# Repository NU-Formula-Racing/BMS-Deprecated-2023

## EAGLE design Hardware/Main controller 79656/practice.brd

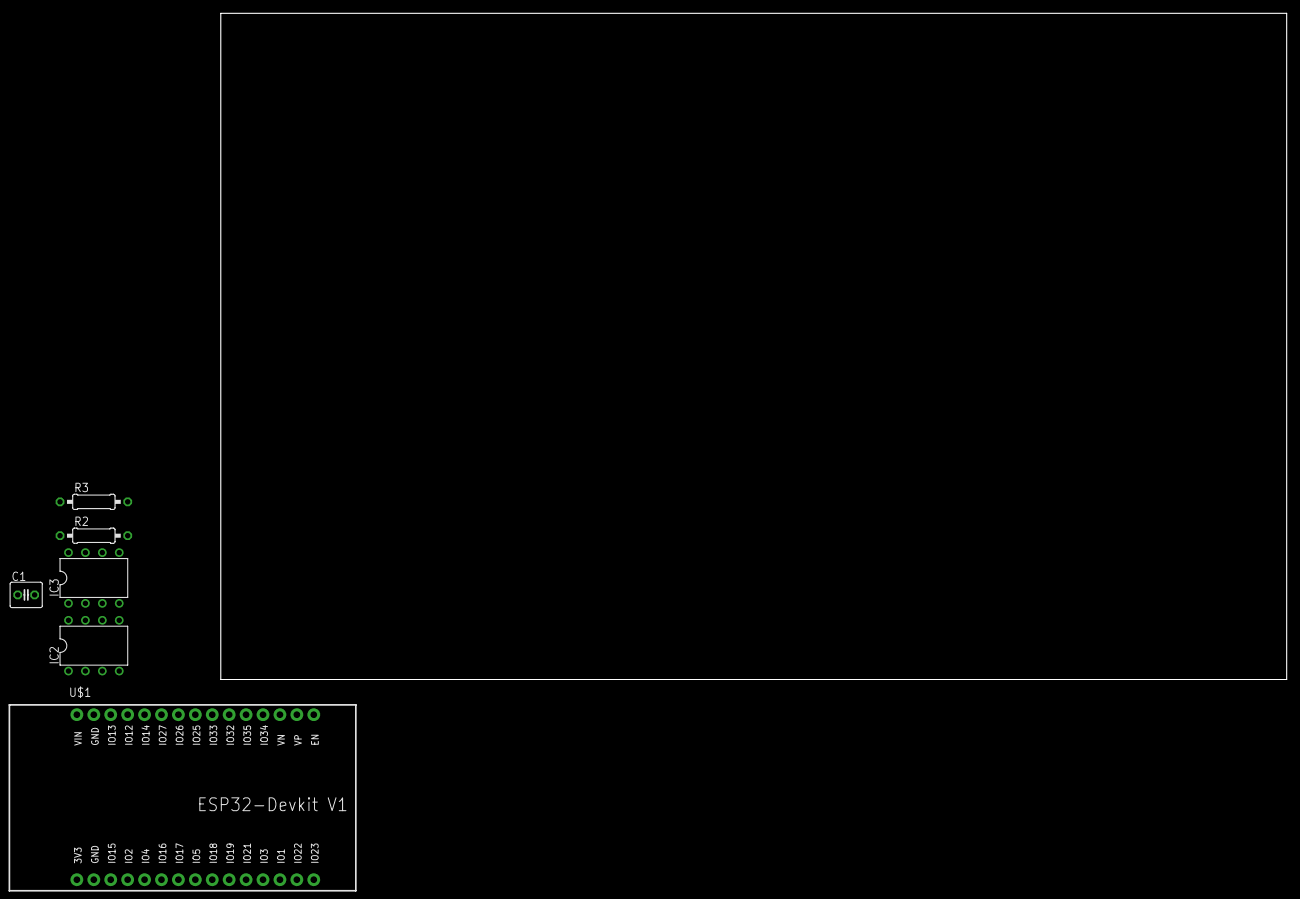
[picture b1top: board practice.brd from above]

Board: 2 copper layers, 160.0 x 100.0 mm, 6 parts (0 on the bottom side), 7 nets, no tracks yet.

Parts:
C1: C025-040X050
IC2, IC3: LM741P; DIL08
R2, R3: 0207/10
U$1: ESP32DEVKITV1; ESP32-DEVKITV1

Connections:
unnamed: IC2.5, IC3.5
unnamed: IC2.1, IC3.1
unnamed: IC2.2, IC2.6, IC3.2, IC3.6
unnamed: IC2.8, IC3.8
unnamed: IC2.7, IC3.7
unnamed: IC2.4, IC3.4
unnamed: C1.1, IC2.3, IC3.3, R2.1, R3.2

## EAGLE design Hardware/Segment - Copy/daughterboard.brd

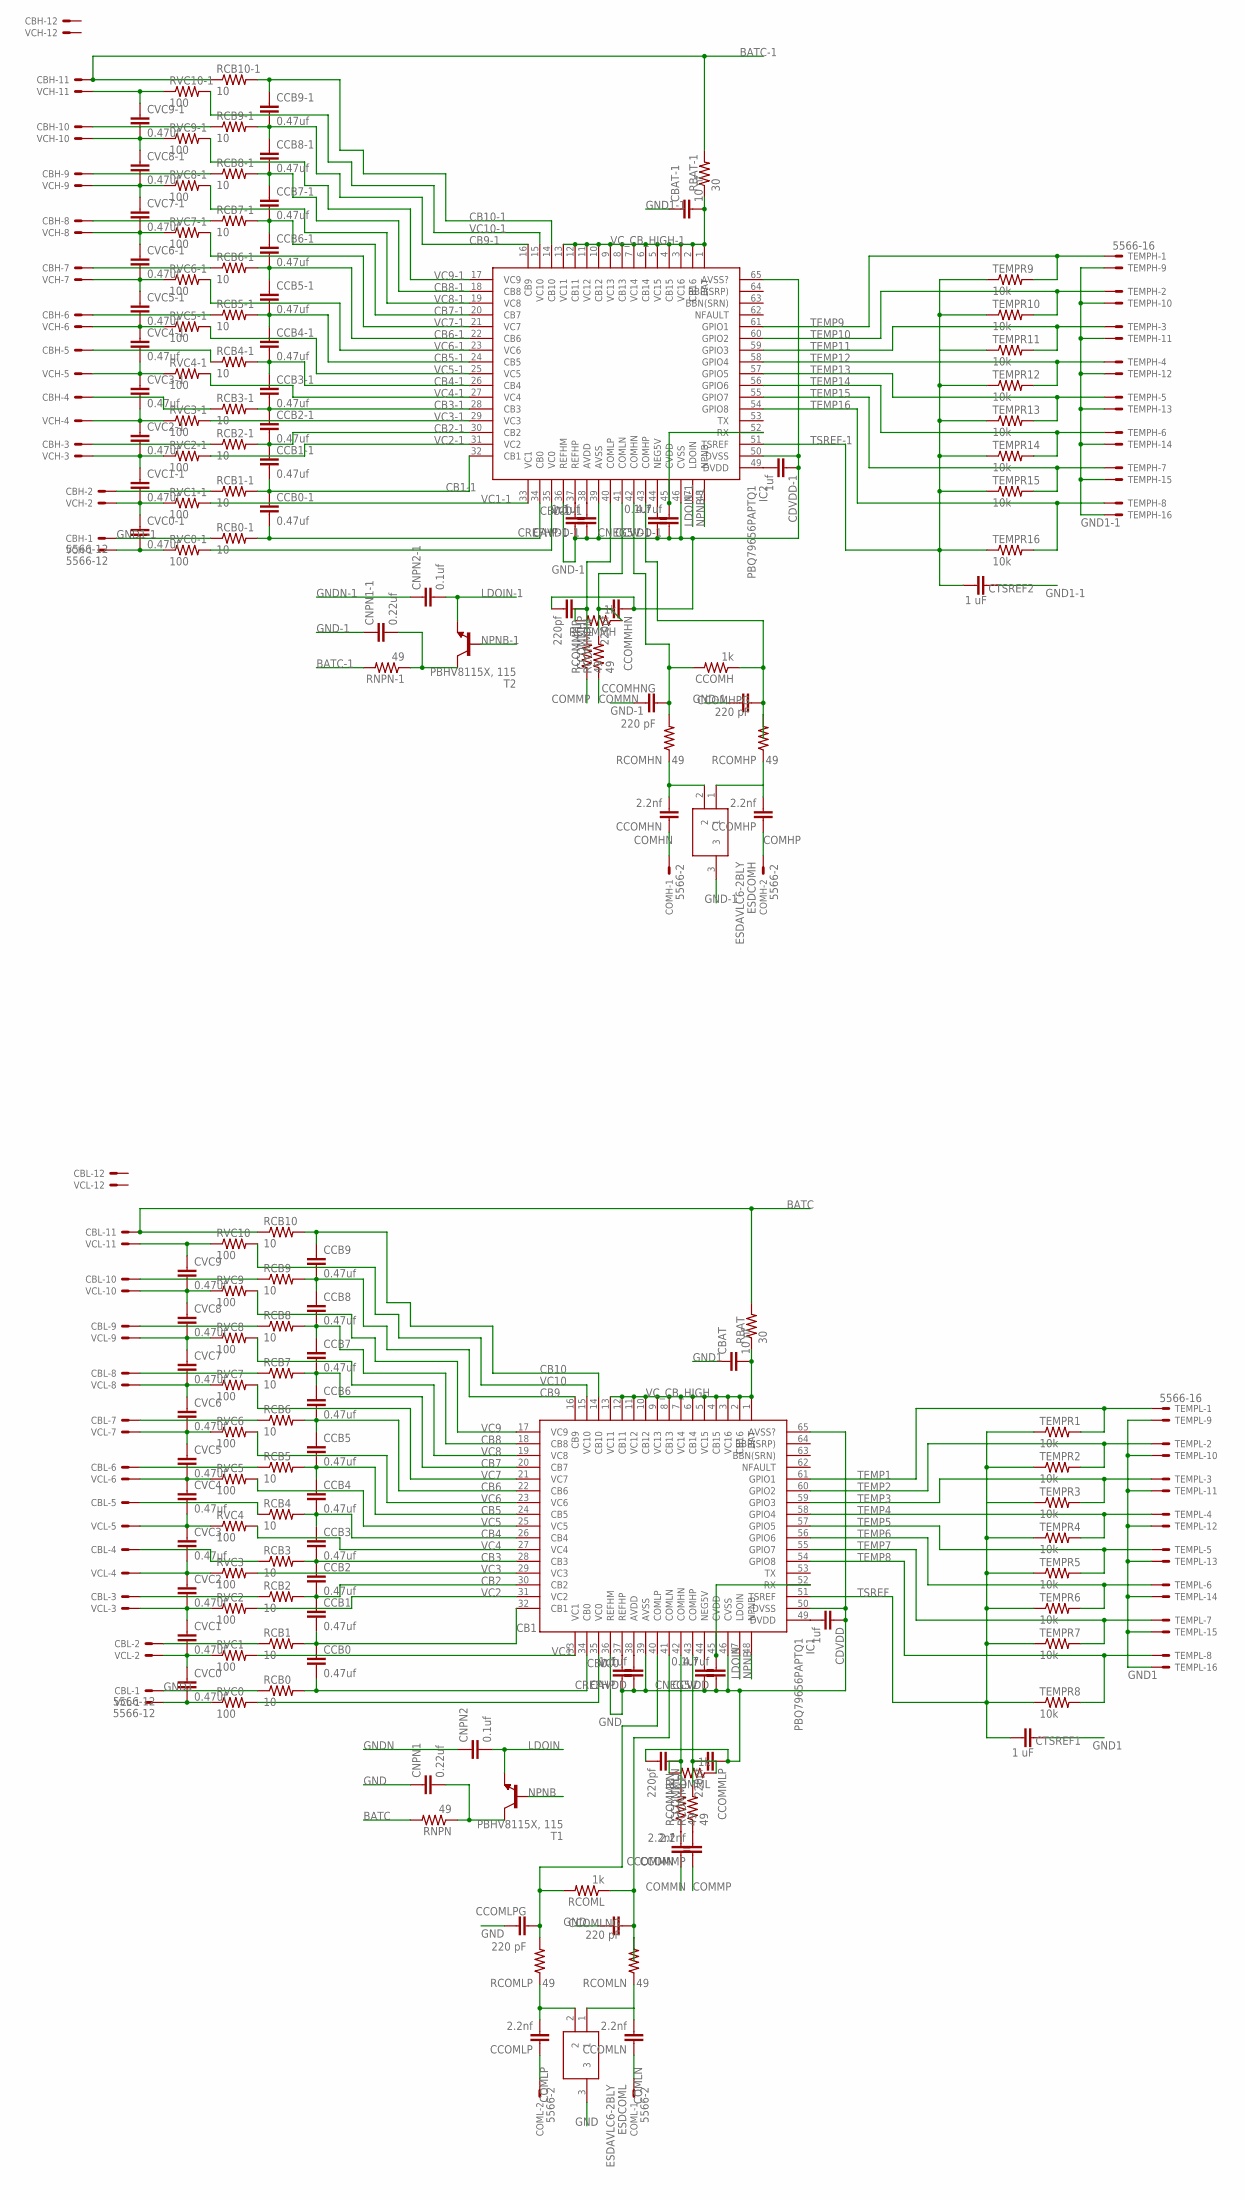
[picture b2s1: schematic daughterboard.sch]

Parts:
CAVDD: 1uf; C0603
CAVDD-1: 1uf; C0603
CBAT: 10 nf; C0603
CBAT-1: 10 nf; C0603
CBH: 5566-12
CBL: 5566-12
CCB0, CCB0-1, CCB1, CCB1-1, CCB2, CCB2-1, CCB3, CCB3-1, CCB4, CCB4-1, CCB5, CCB5-1, CCB6, CCB6-1, CCB7, CCB7-1, CCB8, CCB8-1, CCB9, CCB9-1: 0.47uf; C0603
CCOMH: 1k; R0603
CCOMHN: 2.2nf; C0603
CCOMHNG: 220 pF; C0603
CCOMHP: 2.2nf; C0603
CCOMHPG: 220 pF; C0603
CCOMLN: 2.2nf; C0603
CCOMLNG: 220 pF; C0603
CCOMLP: 2.2nf; C0603
CCOMLPG: 220 pF; C0603
CCOMMHN: 220pf; C0603
CCOMMHP: 220pf; C0603
CCOMMLN: 220pf; C0603
CCOMMLP: 220pf; C0603
CCOMMN: 2.2nf; C0603
CCOMMP: 2.2nf; C0603
CCVDD: 4.7uf; C0603
CCVDD-1: 4.7uf; C0603
CDVDD: 1uf; C0603
CDVDD-1: 1uf; C0603
CNEG5V, CNEG5V-1: 0.1uf; C0603
CNPN1, CNPN1-1: 0.22uf; C0603
CNPN2, CNPN2-1: 0.1uf; C0603
COMH: 5566-2
COML: 5566-2
CREFHP: 1uf; C0603
CREFHP-1: 1uf; C0603
CTSREF1, CTSREF2: 1 uF; C0603
CVC0, CVC0-1, CVC1, CVC1-1, CVC2, CVC2-1, CVC3, CVC3-1, CVC4, CVC4-1, CVC5, CVC5-1, CVC6, CVC6-1, CVC7, CVC7-1, CVC8, CVC8-1, CVC9, CVC9-1: 0.47uf; C0603
ESDCOMH: ESDAVLC6-2BLY; SOT95P255X150-3N
ESDCOML: ESDAVLC6-2BLY; SOT95P255X150-3N
IC1, IC2: PBQ79656PAPTQ1; QFP50P1200X1200X120-65N
RBAT: 30; R0603
RBAT-1: 30; R0603
RCB0, RCB0-1, RCB1, RCB1-1, RCB2, RCB2-1, RCB3, RCB3-1, RCB4, RCB4-1, RCB5, RCB5-1, RCB6, RCB6-1, RCB7, RCB7-1, RCB8, RCB8-1, RCB9, RCB9-1, RCB10, RCB10-1: 10; R1210
RCOMHN: 49; R0603
RCOMHP: 49; R0603
RCOML: 1k; R0603
RCOMLN: 49; R0603
RCOMLP: 49; R0603
RCOMMH: 1k; R0603
RCOMMHN: 49; R0603
RCOMMHP: 49; R0603
RCOMML: 1k; R0603
RCOMMLN: 49; R0603
RCOMMLP: 49; R0603
RNPN: 49; R0603
RNPN-1: 49; R0603
RVC0, RVC0-1, RVC1, RVC1-1, RVC2, RVC2-1, RVC3, RVC3-1, RVC4, RVC4-1, RVC5, RVC5-1, RVC6, RVC6-1, RVC7, RVC7-1, RVC8, RVC8-1, RVC9, RVC9-1, RVC10, RVC10-1: 100; R0603
T1, T2: PBHV8115X, 115; SOT89-BCE
TEMPH: 5566-16
TEMPL: 5566-16
TEMPR1, TEMPR2, TEMPR3, TEMPR4, TEMPR5, TEMPR6, TEMPR7, TEMPR8, TEMPR9, TEMPR10, TEMPR11, TEMPR12, TEMPR13, TEMPR14, TEMPR15, TEMPR16: 10k; R0603
VCH: 5566-12
VCL: 5566-12

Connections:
BATC: CBL.11, RBAT.2, RCB10.1, RNPN.2
BATC-1: CBH.11, RBAT-1.2, RCB10-1.1, RNPN-1.2
CB0: CCB0.2, IC1.34 (CB0), RCB0.2
CB0-1: CCB0-1.2, IC2.34 (CB0), RCB0-1.2
CB1: CCB0.1, CCB1.2, IC1.32 (CB1), RCB1.2
CB1-1: CCB0-1.1, CCB1-1.2, IC2.32 (CB1), RCB1-1.2
CB2: CCB1.1, CCB2.2, IC1.30 (CB2), RCB2.2
CB2-1: CCB1-1.1, CCB2-1.2, IC2.30 (CB2), RCB2-1.2
CB3: CCB2.1, CCB3.2, IC1.28 (CB3), RCB3.2
CB3-1: CCB2-1.1, CCB3-1.2, IC2.28 (CB3), RCB3-1.2
CB4: CCB3.1, CCB4.2, IC1.26 (CB4), RCB4.2
CB4-1: CCB3-1.1, CCB4-1.2, IC2.26 (CB4), RCB4-1.2
CB5: CCB4.1, CCB5.2, IC1.24 (CB5), RCB5.2
CB5-1: CCB4-1.1, CCB5-1.2, IC2.24 (CB5), RCB5-1.2
CB6: CCB5.1, CCB6.2, IC1.22 (CB6), RCB6.2
CB6-1: CCB5-1.1, CCB6-1.2, IC2.22 (CB6), RCB6-1.2
CB7: CCB6.1, CCB7.2, IC1.20 (CB7), RCB7.2
CB7-1: CCB6-1.1, CCB7-1.2, IC2.20 (CB7), RCB7-1.2
CB8: CCB7.1, CCB8.2, IC1.18 (CB8), RCB8.2
CB8-1: CCB7-1.1, CCB8-1.2, IC2.18 (CB8), RCB8-1.2
CB9: CCB8.1, CCB9.2, IC1.16 (CB9), RCB9.2
CB9-1: CCB8-1.1, CCB9-1.2, IC2.16 (CB9), RCB9-1.2
CB10: CCB9.1, IC1.14 (CB10), RCB10.2
CB10-1: CCB9-1.1, IC2.14 (CB10), RCB10-1.2
COMHN: CCOMHN.1, COMH.1
COMHP: CCOMHP.1, COMH.2
COMLN: CCOMLN.1, COML.1
COMLP: CCOMLP.1, COML.2
COMMN: CCOMMN.1, RCOMMHN.1
COMMP: CCOMMP.1, RCOMMHP.1
CVDD: CCVDD.2, IC1.45 (CVDD), IC1.52 (RX)
CVDD-1: CCVDD-1.2, IC2.45 (CVDD), IC2.52 (RX)
GND: CAVDD.1, CCOMLNG.1, CCOMLPG.1, CCOMMLN.2, CCOMMLP.1, CCVDD.1, CDVDD.1, CNEG5V.1, CNPN1.1, CREFHP.1, ESDCOML.3, IC1.36 (REFHM), IC1.39 (AVSS), IC1.46 (CVSS), IC1.50 (DVSS), IC1.65 (AVSS?)
GND1: CBAT.1, CBL.1, CTSREF1.1, RCB0.1, TEMPL.9, TEMPL.10, TEMPL.11, TEMPL.12, TEMPL.13, TEMPL.14, TEMPL.15, TEMPL.16
GND1-1: CBAT-1.1, CBH.1, CTSREF2.1, RCB0-1.1, TEMPH.9, TEMPH.10, TEMPH.11, TEMPH.12, TEMPH.13, TEMPH.14, TEMPH.15, TEMPH.16
GND-1: CAVDD-1.1, CCOMHNG.1, CCOMHPG.1, CCOMMHN.1, CCOMMHP.2, CCVDD-1.1, CDVDD-1.1, CNEG5V-1.1, CNPN1-1.1, CREFHP-1.1, ESDCOMH.3, IC2.36 (REFHM), IC2.39 (AVSS), IC2.46 (CVSS), IC2.50 (DVSS), IC2.65 (AVSS?)
GNDN: CNPN2.1
GNDN-1: CNPN2-1.1
LDOIN: CNPN2.2, IC1.47 (LDOIN), T1.E
LDOIN-1: CNPN2-1.2, IC2.47 (LDOIN), T2.E
unnamed: CBL.2, RCB1.1
unnamed: CBL.3, RCB2.1
unnamed: CBL.4, RCB3.1
unnamed: CBL.5, RCB4.1
unnamed: CBL.6, RCB5.1
unnamed: CBL.9, RCB8.1
unnamed: CBL.10, RCB9.1
unnamed: CBL.7, RCB6.1
unnamed: CCOMLNG.2, IC1.41 (COMLN), RCOML.1, RCOMLN.2
unnamed: CBL.8, RCB7.1
unnamed: CREFHP.2, IC1.37 (REFHP)
unnamed: CVC0.2, RVC0.1, VCL.1
unnamed: CVC0.1, CVC1.2, RVC1.1, VCL.2
unnamed: CVC1.1, CVC2.2, RVC2.1, VCL.3
unnamed: CVC2.1, CVC3.2, RVC3.1, VCL.4
unnamed: CVC3.1, CVC4.2, RVC4.1, VCL.5
unnamed: CVC4.1, CVC5.2, RVC5.1, VCL.6
unnamed: CVC5.1, CVC6.2, RVC6.1, VCL.7
unnamed: CVC6.1, CVC7.2, RVC7.1, VCL.8
unnamed: CVC7.1, CVC8.2, RVC8.1, VCL.9
unnamed: CVC8.1, CVC9.2, RVC9.1, VCL.10
unnamed: CVC9.1, RVC10.1, VCL.11
unnamed: CAVDD.2, IC1.38 (AVDD)
unnamed: CNEG5V.2, IC1.44 (NEG5V)
unnamed: CCOMLPG.2, IC1.40 (COMLP), RCOML.2, RCOMLP.2
unnamed: CDVDD.2, IC1.49 (DVDD)
unnamed: CCOMMLN.1, IC1.42 (COMHN), RCOMML.2, RCOMMLN.2
unnamed: CCOMMLP.2, IC1.43 (COMHP), RCOMML.1, RCOMMLP.2
unnamed: CCOMMN.2, RCOMMLN.1
unnamed: CCOMMP.2, RCOMMLP.1
unnamed: CNPN1.2, RNPN.1, T1.C
unnamed: CCOMLP.2, ESDCOML.2, RCOMLP.1
unnamed: CCOMLN.2, ESDCOML.1, RCOMLN.1
unnamed: CBH.3, RCB2-1.1
unnamed: CBH.2, RCB1-1.1
unnamed: CBH.4, RCB3-1.1
unnamed: CBH.5, RCB4-1.1
unnamed: CBH.6, RCB5-1.1
unnamed: CBH.7, RCB6-1.1
unnamed: CBH.8, RCB7-1.1
unnamed: CBH.9, RCB8-1.1
unnamed: CBH.10, RCB9-1.1
unnamed: CVC0-1.2, RVC0-1.1, VCH.1
unnamed: CVC0-1.1, CVC1-1.2, RVC1-1.1, VCH.2
unnamed: CVC1-1.1, CVC2-1.2, RVC2-1.1, VCH.3
unnamed: CVC2-1.1, CVC3-1.2, RVC3-1.1, VCH.4
unnamed: CVC3-1.1, CVC4-1.2, RVC4-1.1, VCH.5
unnamed: CVC4-1.1, CVC5-1.2, RVC5-1.1, VCH.6
unnamed: CVC5-1.1, CVC6-1.2, RVC6-1.1, VCH.7
unnamed: CVC6-1.1, CVC7-1.2, RVC7-1.1, VCH.8
unnamed: CVC7-1.1, CVC8-1.2, RVC8-1.1, VCH.9
unnamed: CVC8-1.1, CVC9-1.2, RVC9-1.1, VCH.10
unnamed: CVC9-1.1, RVC10-1.1, VCH.11
unnamed: CREFHP-1.2, IC2.37 (REFHP)
unnamed: CAVDD-1.2, IC2.38 (AVDD)
unnamed: CNEG5V-1.2, IC2.44 (NEG5V)
unnamed: CDVDD-1.2, IC2.49 (DVDD)
unnamed: CCOMMHN.2, IC2.41 (COMLN), RCOMMH.1, RCOMMHN.2
unnamed: CCOMMHP.1, IC2.40 (COMLP), RCOMMH.2, RCOMMHP.2
unnamed: CNPN1-1.2, RNPN-1.1, T2.C
unnamed: CCOMH.1, CCOMHPG.2, IC2.43 (COMHP), RCOMHP.2
unnamed: CCOMH.2, CCOMHNG.2, IC2.42 (COMHN), RCOMHN.2
unnamed: CCOMHN.2, ESDCOMH.2, RCOMHN.1
unnamed: CCOMHP.2, ESDCOMH.1, RCOMHP.1
NPNB: IC1.48 (NPNB), T1.B
NPNB-1: IC2.48 (NPNB), T2.B
TEMP1: IC1.61 (GPIO1), TEMPL.1, TEMPR1.2
TEMP2: IC1.60 (GPIO2), TEMPL.2, TEMPR2.2
TEMP3: IC1.59 (GPIO3), TEMPL.3, TEMPR3.2
TEMP4: IC1.58 (GPIO4), TEMPL.4, TEMPR4.2
TEMP5: IC1.57 (GPIO5), TEMPL.5, TEMPR5.2
TEMP6: IC1.56 (GPIO6), TEMPL.6, TEMPR6.2
TEMP7: IC1.55 (GPIO7), TEMPL.7, TEMPR7.2
TEMP8: IC1.54 (GPIO8), TEMPL.8, TEMPR8.2
TEMP9: IC2.61 (GPIO1), TEMPH.1, TEMPR9.2
TEMP10: IC2.60 (GPIO2), TEMPH.2, TEMPR10.2
TEMP11: IC2.59 (GPIO3), TEMPH.3, TEMPR11.2
TEMP12: IC2.58 (GPIO4), TEMPH.4, TEMPR12.2
TEMP13: IC2.57 (GPIO5), TEMPH.5, TEMPR13.2
TEMP14: IC2.56 (GPIO6), TEMPH.6, TEMPR14.2
TEMP15: IC2.55 (GPIO7), TEMPH.7, TEMPR15.2
TEMP16: IC2.54 (GPIO8), TEMPH.8, TEMPR16.2
TSREF: CTSREF1.2, IC1.51 (TSREF), TEMPR1.1, TEMPR2.1, TEMPR3.1, TEMPR4.1, TEMPR5.1, TEMPR6.1, TEMPR7.1, TEMPR8.1
TSREF-1: CTSREF2.2, IC2.51 (TSREF), TEMPR9.1, TEMPR10.1, TEMPR11.1, TEMPR12.1, TEMPR13.1, TEMPR14.1, TEMPR15.1, TEMPR16.1
VC0: IC1.35 (VC0), RVC0.2
VC0-1: IC2.35 (VC0), RVC0-1.2
VC1: IC1.33 (VC1), RVC1.2
VC1-1: IC2.33 (VC1), RVC1-1.2
VC2: IC1.31 (VC2), RVC2.2
VC2-1: IC2.31 (VC2), RVC2-1.2
VC3: IC1.29 (VC3), RVC3.2
VC3-1: IC2.29 (VC3), RVC3-1.2
VC4: IC1.27 (VC4), RVC4.2
VC4-1: IC2.27 (VC4), RVC4-1.2
VC5: IC1.25 (VC5), RVC5.2
VC5-1: IC2.25 (VC5), RVC5-1.2
VC6: IC1.23 (VC6), RVC6.2
VC6-1: IC2.23 (VC6), RVC6-1.2
VC7: IC1.21 (VC7), RVC7.2
VC7-1: IC2.21 (VC7), RVC7-1.2
VC8: IC1.19 (VC8), RVC8.2
VC8-1: IC2.19 (VC8), RVC8-1.2
VC9: IC1.17 (VC9), RVC9.2
VC9-1: IC2.17 (VC9), RVC9-1.2
VC10: IC1.15 (VC10), RVC10.2
VC10-1: IC2.15 (VC10), RVC10-1.2
VC_CB_HIGH: CBAT.2, IC1.1 (BAT), IC1.2 (CB16), IC1.3 (VC16), IC1.4 (CB15), IC1.5 (VC15), IC1.6 (CB14), IC1.7 (VC14), IC1.8 (CB13), IC1.9 (VC13), IC1.10 (CB12), IC1.11 (VC12), IC1.12 (CB11), IC1.13 (VC11), RBAT.1
VC_CB_HIGH-1: CBAT-1.2, IC2.1 (BAT), IC2.2 (CB16), IC2.3 (VC16), IC2.4 (CB15), IC2.5 (VC15), IC2.6 (CB14), IC2.7 (VC14), IC2.8 (CB13), IC2.9 (VC13), IC2.10 (CB12), IC2.11 (VC12), IC2.12 (CB11), IC2.13 (VC11), RBAT-1.1

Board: 2 copper layers, 162 parts (0 on the bottom side), 146 nets, no tracks yet.

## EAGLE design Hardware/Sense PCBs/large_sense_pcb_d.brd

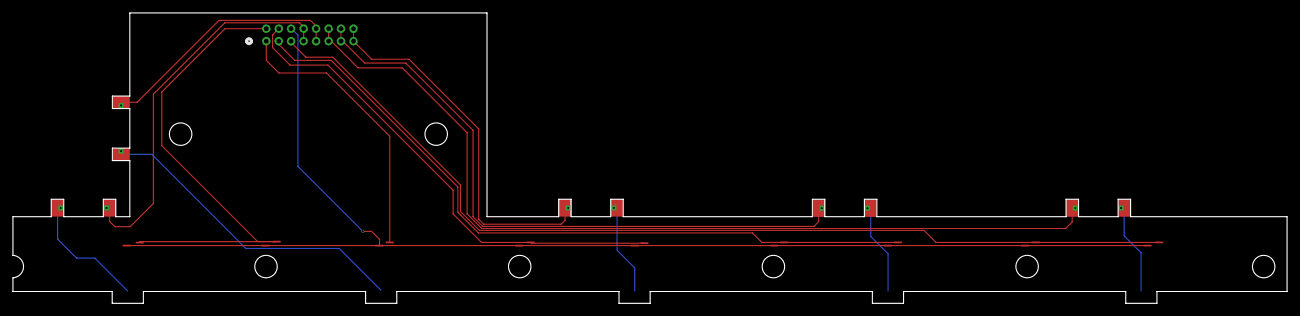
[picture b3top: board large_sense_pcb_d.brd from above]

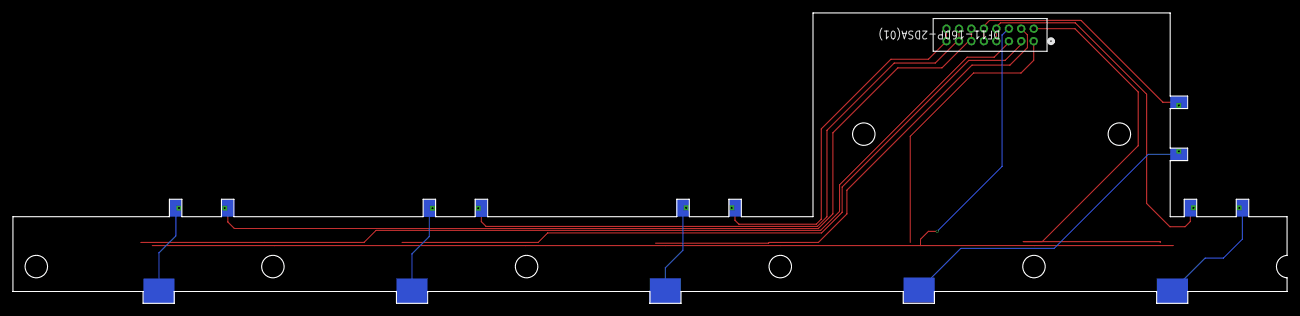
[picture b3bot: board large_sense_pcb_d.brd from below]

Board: 2 copper layers, 204.4 x 46.6 mm, 29 parts (6 on the bottom side), 16 nets.

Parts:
J1: DF11-16DP-2DSA(01); CONN_DF11-16DP-2DSA(01)_HIR
U$1, U$2, U$3, U$4, U$5: FUSE; FUSE_PADS
U$6, U$7, U$8, U$9, U$10: BB_CONTACT
U$12, U$13, U$14, U$15, U$16, U$17, U$18, U$19, U$20, U$22, U$23, U$24, U$25, U$26, U$27, U$28, U$29, U$30: THERM_PIN

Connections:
unnamed: J1.15, J1.16, U$5.P$1, U$5.P$3, U$5.P$5
unnamed: U$1.P$2, U$1.P$4, U$1.P$6, U$6.P$1
unnamed: J1.7, J1.8, U$1.P$1, U$1.P$3, U$1.P$5
unnamed: U$2.P$2, U$2.P$4, U$2.P$6, U$7.P$1
unnamed: U$5.P$2, U$5.P$4, U$5.P$6, U$10.P$1
unnamed: U$3.P$2, U$3.P$4, U$3.P$6, U$8.P$1
unnamed: J1.13, J1.14, U$4.P$1, U$4.P$3, U$4.P$5
unnamed: U$4.P$2, U$4.P$4, U$4.P$6, U$9.P$1
unnamed: J1.11, J1.12, U$3.P$1, U$3.P$3, U$3.P$5
unnamed: J1.9, J1.10, U$2.P$1, U$2.P$3, U$2.P$5
THERM1: J1.5, U$22.P$1, U$23.P$1
THERM2: J1.4, U$24.P$1, U$25.P$1
THERM3: J1.3, U$26.P$1, U$27.P$1
THERM4: J1.2, U$28.P$1, U$29.P$1
THERM5: J1.1, U$30.P$1
THERMGND: J1.6, U$12.P$1, U$13.P$1, U$14.P$1, U$15.P$1, U$16.P$1, U$17.P$1, U$18.P$1, U$19.P$1, U$20.P$1

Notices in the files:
parts and their libraries:
COPYRIGHT: Copyright (C) 2023 Ultra Librarian. All rights reserved.
